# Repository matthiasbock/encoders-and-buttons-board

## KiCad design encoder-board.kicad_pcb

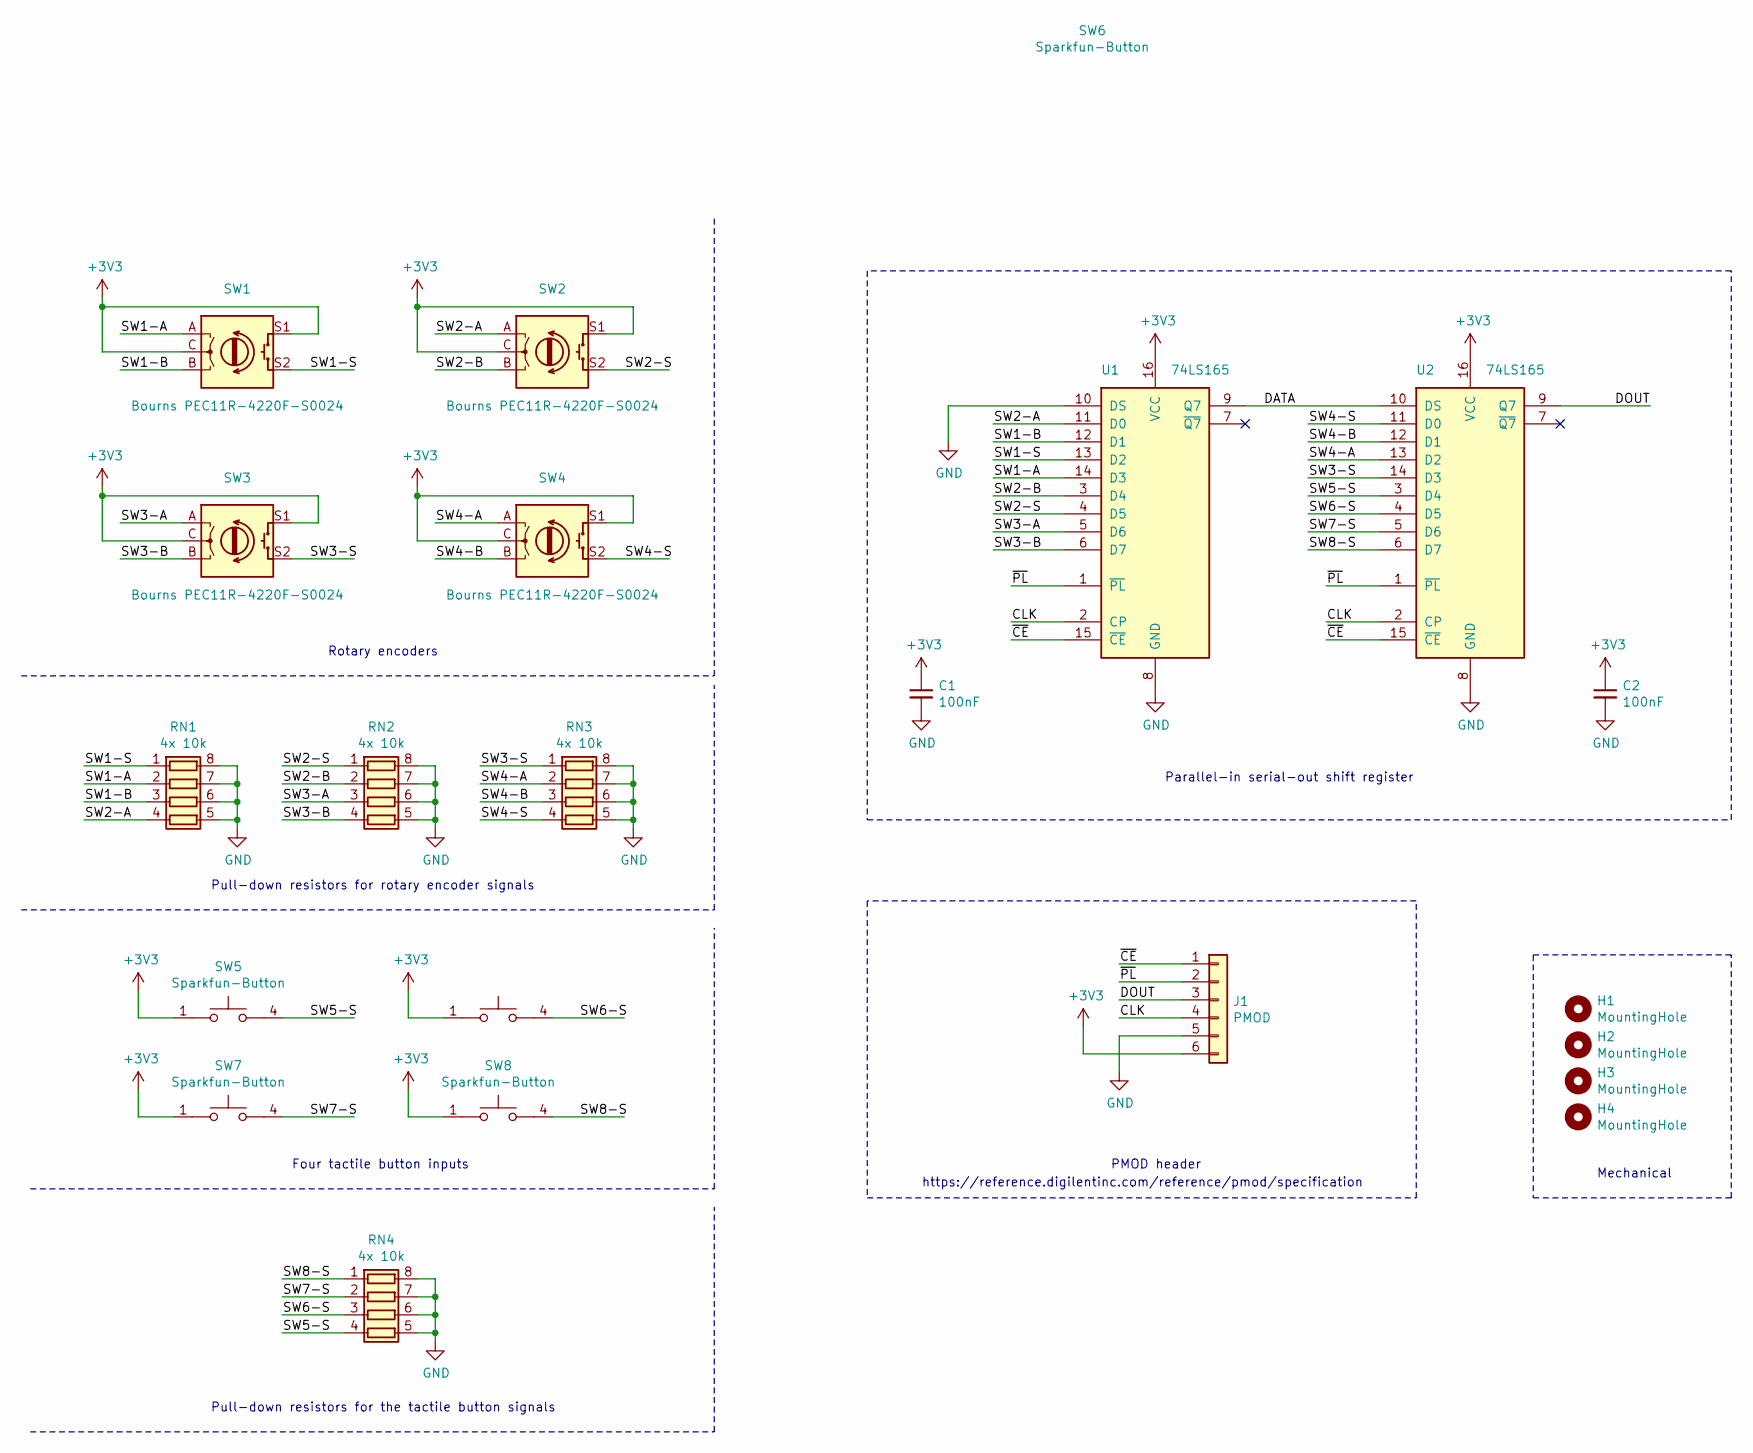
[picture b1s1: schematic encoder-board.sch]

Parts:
C1, C2: 100nF; C_0805_2012Metric_Pad1.15x1.40mm_HandSolder
H1, H2, H3, H4: MountingHole; MountingHole_2.5mm
J1: PMOD; PinHeader_1x06_P2.54mm_Vertical
RN1, RN2, RN3, RN4: 4x 10k; Bourns-CAY16
SW1, SW2, SW3, SW4: Bourns PEC11R-4220F-S0024; Bourns-PEC11R
SW5, SW6, SW7, SW8: Sparkfun-Button
U1, U2: 74LS165; SOIC-16_3.9x9.9mm_P1.27mm

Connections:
+3V3: C1.1, C2.1, J1.6, SW1.C, SW1.S1, SW2.C, SW2.S1, SW3.C, SW3.S1, SW4.C, SW4.S1, SW5.1, SW5.2, SW6.1, SW6.2, SW7.1, SW7.2, SW8.1, SW8.2, U1.16 (VCC), U2.16 (VCC)
/CLK: J1.4, U1.2 (CP), U2.2 (CP)
/DATA: U1.9 (Q7), U2.10 (DS)
/DOUT: J1.3, U2.9 (Q7)
/SW1-A: RN1.2 (R2.1), SW1.A, U1.14 (D3)
/SW1-B: RN1.3 (R3.1), SW1.B, U1.12 (D1)
/SW1-S: RN1.1 (R1.1), SW1.S2, U1.13 (D2)
/SW2-A: RN1.4 (R4.1), SW2.A, U1.11 (D0)
/SW2-B: RN2.2 (R2.1), SW2.B, U1.3 (D4)
/SW2-S: RN2.1 (R1.1), SW2.S2, U1.4 (D5)
/SW3-A: RN2.3 (R3.1), SW3.A, U1.5 (D6)
/SW3-B: RN2.4 (R4.1), SW3.B, U1.6 (D7)
/SW3-S: RN3.1 (R1.1), SW3.S2, U2.14 (D3)
/SW4-A: RN3.2 (R2.1), SW4.A, U2.13 (D2)
/SW4-B: RN3.3 (R3.1), SW4.B, U2.12 (D1)
/SW4-S: RN3.4 (R4.1), SW4.S2, U2.11 (D0)
/SW5-S: RN4.4 (R4.1), SW5.3, SW5.4, U2.3 (D4)
/SW6-S: RN4.3 (R3.1), SW6.3, SW6.4, U2.4 (D5)
/SW7-S: RN4.2 (R2.1), SW7.3, SW7.4, U2.5 (D6)
/SW8-S: RN4.1 (R1.1), SW8.3, SW8.4, U2.6 (D7)
/~CE: J1.1, U1.15 (~CE), U2.15 (~CE)
/~PL: J1.2, U1.1 (~PL), U2.1 (~PL)
GND: C1.2, C2.2, J1.5, RN1.5 (R4.2), RN1.6 (R3.2), RN1.7 (R2.2), RN1.8 (R1.2), RN2.5 (R4.2), RN2.6 (R3.2), RN2.7 (R2.2), RN2.8 (R1.2), RN3.5 (R4.2), RN3.6 (R3.2), RN3.7 (R2.2), RN3.8 (R1.2), RN4.5 (R4.2), RN4.6 (R3.2), RN4.7 (R2.2), RN4.8 (R1.2), U1.8 (GND), U1.10 (DS), U2.8 (GND)

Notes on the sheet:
Rotary encoders
Pull-down resistors for rotary encoder signals
Four tactile button inputs
Pull-down resistors for the tactile button signals
Parallel-in serial-out shift register
PMOD header
https://reference.digilentinc.com/reference/pmod/specification
Mechanical

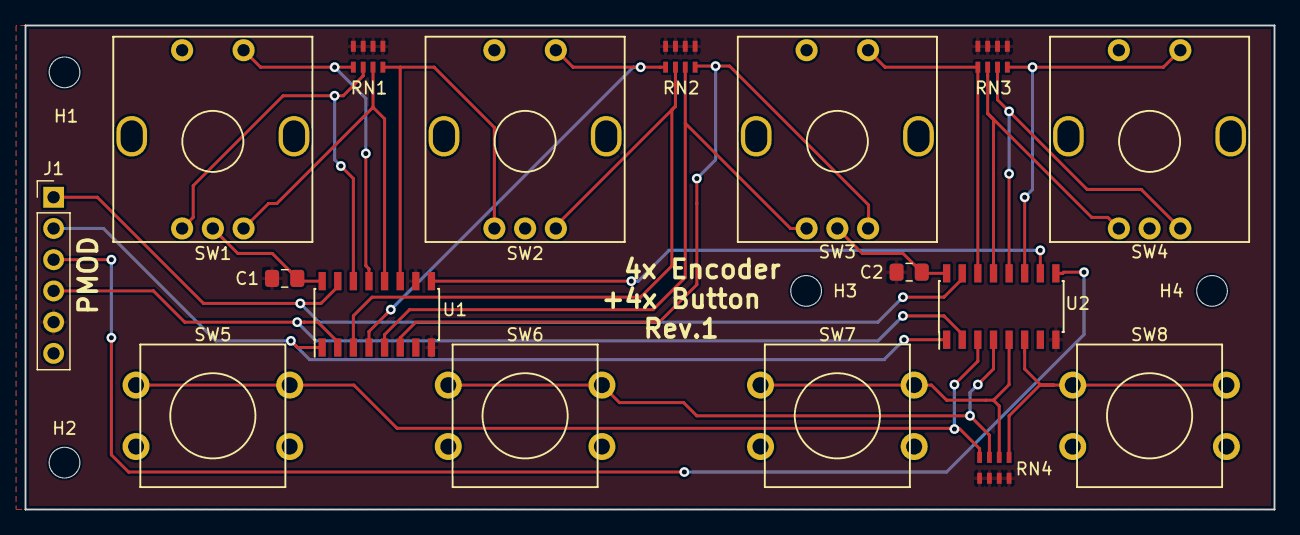
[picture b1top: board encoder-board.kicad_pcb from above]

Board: 2 copper layers, 101.6 x 39.4 mm, 21 parts (0 on the bottom side), 23 nets.

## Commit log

2019-02-04 Added KiCad libraries as submodule
2019-02-04 Completed first draft for the schematic
2019-02-05 Using PMOD compatible pin layout
2019-02-05 Finished layouting revision 1
2019-02-05 Added a label to the silkscreen
2019-02-06 Exported fabrication files
2019-03-01 Added CERN Open Hardware Licence v1.2
2019-03-19 Added schematic PDF for revision 1.0
